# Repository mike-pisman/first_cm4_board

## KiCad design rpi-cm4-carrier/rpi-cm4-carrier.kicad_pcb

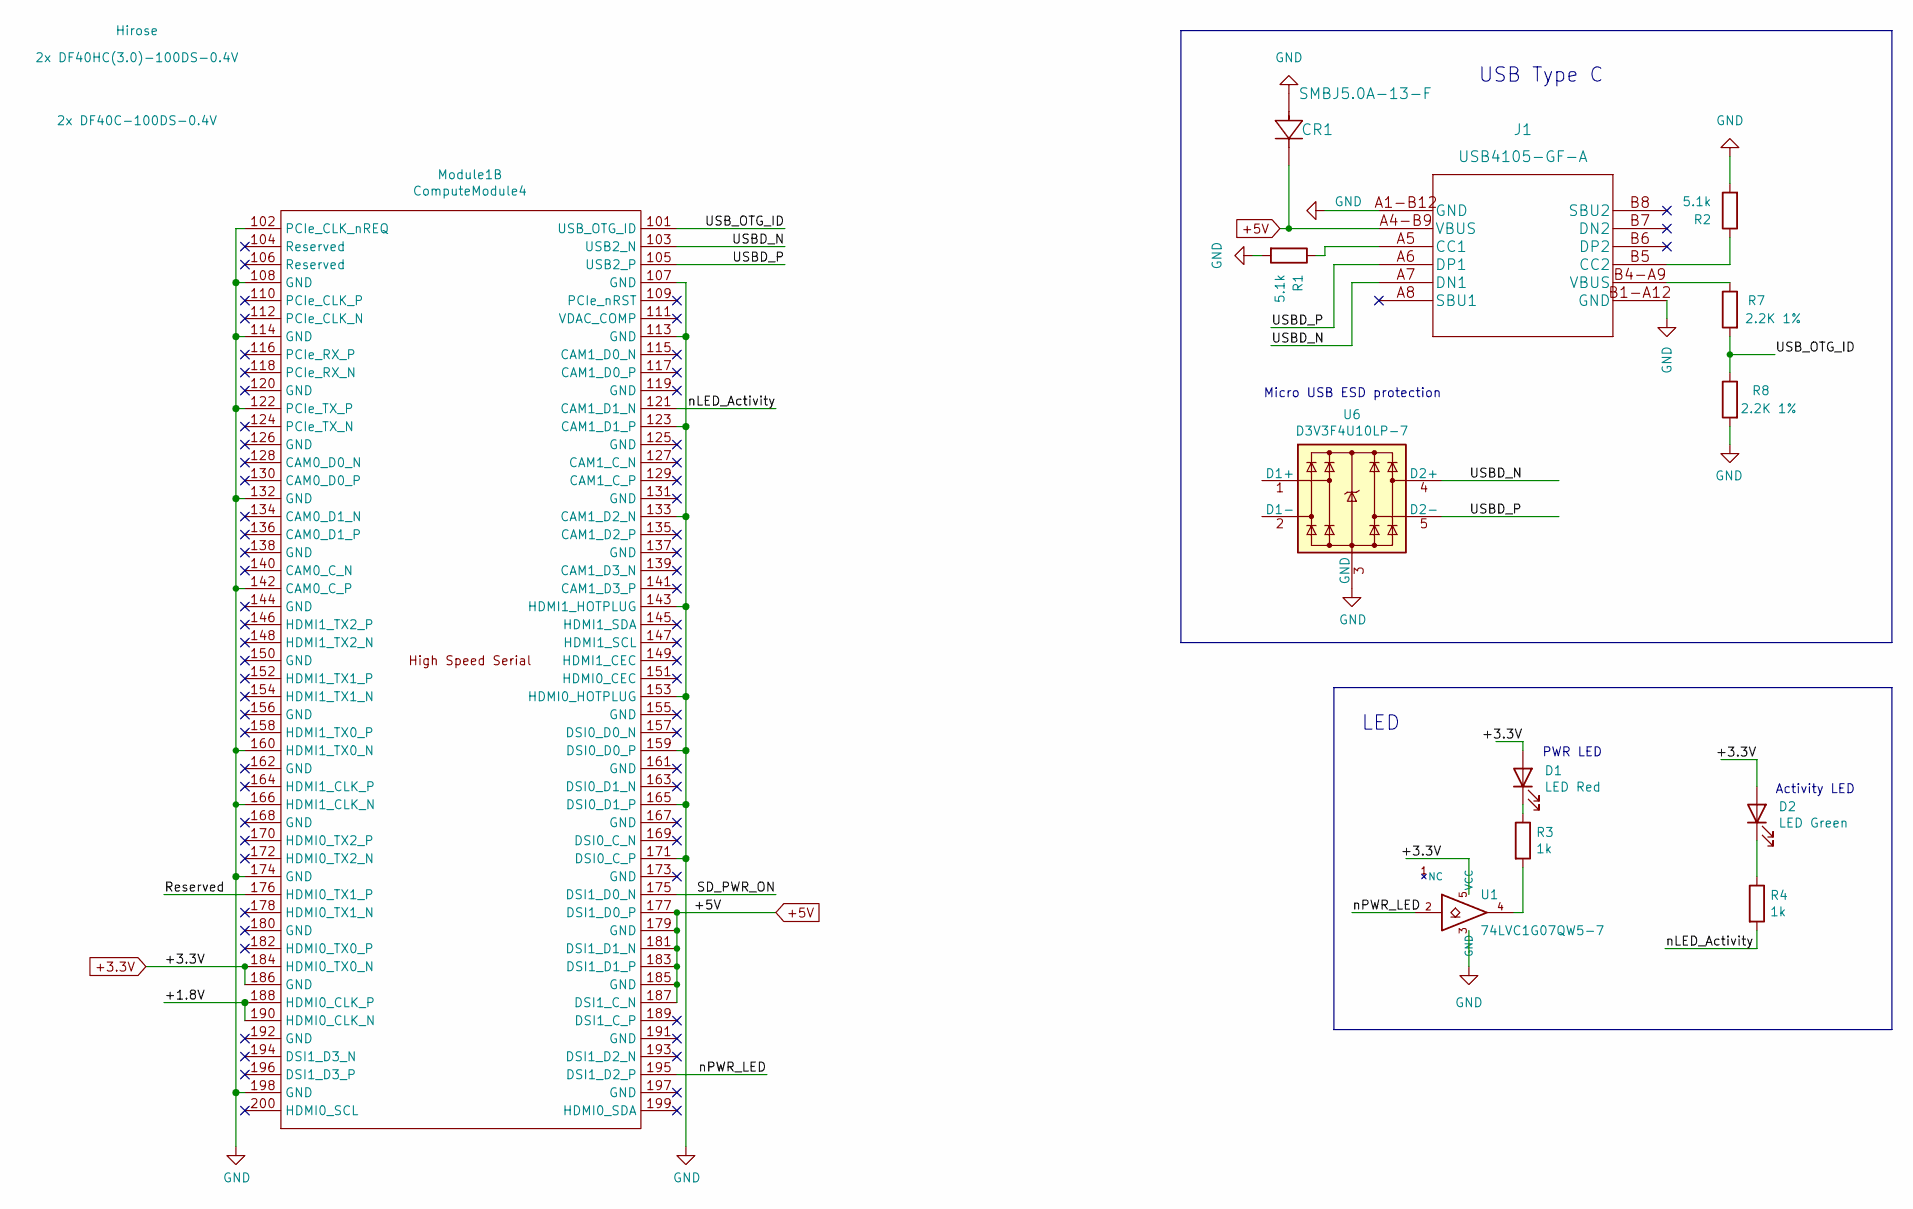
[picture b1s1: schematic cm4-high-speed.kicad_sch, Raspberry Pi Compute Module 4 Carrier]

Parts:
CR1: SMBJ5.0A-13-F; D_SMB; Digi-Key_PN SMBJ5.0A-FDICT-ND
D1: LED Red; LED_0603_1608Metric; Part Description Red 620nm LED Indication - Discrete 2.2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
D2: LED Green; LED_0603_1608Metric; Part Description Green 572nm LED Indication - Discrete 2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
J1: USB4105-GF-A; Digi-Key_PN 2073-USB4105-GF-ACT-ND
Module1: ComputeModule4; Raspberry-Pi-4-Compute-Module; Part Description 100 Position Connector Receptacle, Cent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; Digi-Key_PN 2x H11615CT-ND
R1, R2: 5.1k; R_0201_0603Metric_Pad0.64x0.40mm_HandSolder; Digi-Key_PN 311-5.10KHRCT-ND
R3, R4: 1k; R_0402_1005Metric; Part Description Resistor 1K M1005 1% 63mW
R7, R8: 2.2K 1%; R_0402_1005Metric; Part Description Resistor 2.2K M1005 1% 63mW
U1: 74LVC1G07QW5-7; SOT-353_SC-70-5; Part Description Buffer, Non-Inverting 1 Element 1 Bit p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; Digi-Key_PN 31-74LVC1G07QW5-7CT-ND
U6: D3V3F4U10LP-7; USON-10_2.5x1.0mm_P0.5mm; Part Description Quad TVS diode for high speed signals (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

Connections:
+3.3V: D1.2 (A), D2.2 (A), Module1.184 (HDMI0_TX0_N), Module1.186 (GND), U1.5 (VCC); also elsewhere on the board
+5V: CR1.1, J1.A4-B9 (VBUS), Module1.177 (DSI1_D0_P), Module1.179 (GND), Module1.181 (DSI1_D1_N), Module1.183 (DSI1_D1_P), Module1.185 (GND), Module1.187 (DSI1_C_N); also elsewhere on the board
/CM4 USB and LEDs/+1.8V: Module1.188 (HDMI0_CLK_P), Module1.190 (HDMI0_CLK_N)
/CM4 USB and LEDs/Reserved: Module1.176 (HDMI0_TX1_P)
/CM4 USB and LEDs/SD_PWR_ON: Module1.175 (DSI1_D0_N)
/CM4 USB and LEDs/USBD_N: J1.A7 (DN1), Module1.103 (USB2_N), U6.4 (D2+), U6.7
/CM4 USB and LEDs/USBD_P: J1.A6 (DP1), Module1.105 (USB2_P), U6.5 (D2-), U6.6
/CM4 USB and LEDs/USB_OTG_ID: Module1.101 (USB_OTG_ID), R7.2, R8.1
/CM4 USB and LEDs/nLED_Activity: Module1.121 (CAM1_D1_N), R4.2
/CM4 USB and LEDs/nPWR_LED: Module1.195 (DSI1_D2_P), U1.2
GND: CR1.2, J1.A1-B12 (GND), J1.B1-A12 (GND), Module1.102 (PCIe_CLK_nREQ), Module1.107 (GND), Module1.108 (GND), Module1.113 (GND), Module1.114 (GND), Module1.122 (PCIe_TX_P), Module1.123 (CAM1_D1_P), Module1.132 (GND), Module1.133 (CAM1_D2_N), Module1.142 (CAM0_C_P), Module1.143 (HDMI1_HOTPLUG), Module1.153 (HDMI0_HOTPLUG), Module1.159 (DSI0_D0_P), Module1.160 (HDMI1_TX0_N), Module1.165 (DSI0_D1_P), Module1.166 (HDMI1_CLK_N), Module1.171 (DSI0_C_P), Module1.174 (GND), Module1.198 (GND), R1.2, R2.2, R8.2, U1.3 (GND), U6.3 (GND), U6.8 (GND); also elsewhere on the board
unnamed: D1.1 (K), R3.1
unnamed: D2.1 (K), R4.1
unnamed: J1.A5 (CC1), R1.1
unnamed: J1.B4-A9 (VBUS), R7.1
unnamed: J1.B5 (CC2), R2.1
unnamed: R3.2, U1.4
unnamed: U6.1 (D1+), U6.10
unnamed: U6.2 (D1-), U6.9

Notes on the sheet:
Activity LED
USB Type C
LED
Micro USB ESD protection
PWR LED

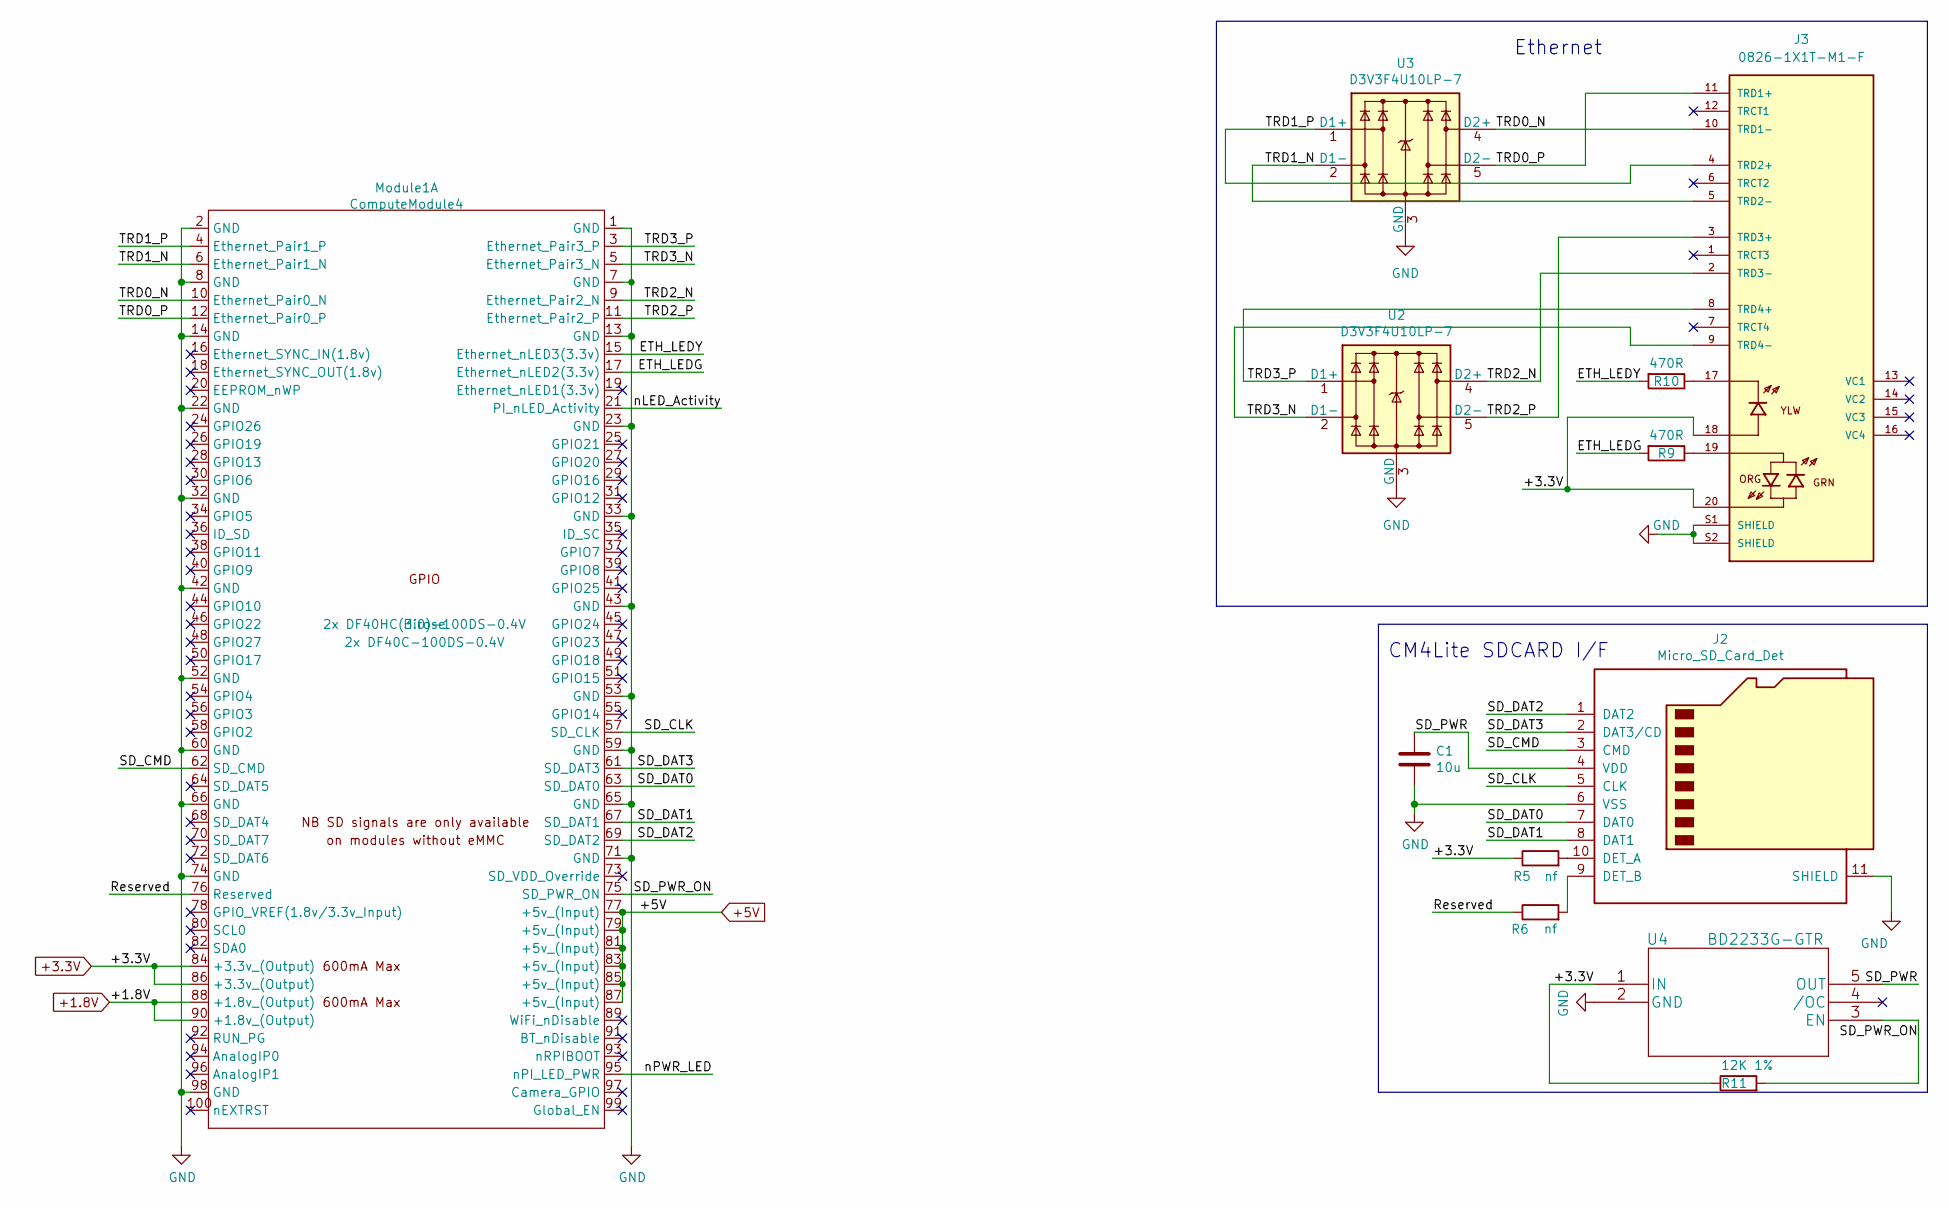
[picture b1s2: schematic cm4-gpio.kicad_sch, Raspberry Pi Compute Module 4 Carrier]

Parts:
C1: 10u; C_0805_2012Metric; Part Description 10uF 10% 10V Ceramic Capacitor X7R 0805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
J2: Micro_SD_Card_Det; SDCARD_MOLEX_503398-1892; Part Description 9 (8 + 1) Position Card Connector micro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; Digi-Key_PN 2073-MEM2051-00-195-00-ACT-ND
J3: 0826-1X1T-M1-F; Digi-Key_PN 380-1122-ND
Module1: ComputeModule4; Raspberry-Pi-4-Compute-Module; Part Description 100 Position Connector Receptacle, Cent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; Digi-Key_PN 2x H11615CT-ND
R5, R6: nf; R_0402_1005Metric; Part Description Resistor 1K M1005 1% 63mW
R9, R10: 470R; R_0402_1005Metric; Part Description Resistor 470R M1005 1% 63mW
R11: 12K 1%; R_0402_1005Metric; Part Description Resistor 12K M1005 1% 63mW
U2, U3: D3V3F4U10LP-7; USON-10_2.5x1.0mm_P0.5mm; Part Description Quad TVS diode for high speed signals (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; Digi-Key_PN D3V3F4U10LP-7DICT-ND
U4: BD2233G-GTR; SOT-23-5

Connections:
+1.8V: Module1.88 (+1.8v_(Output)), Module1.90 (+1.8v_(Output))
+3.3V: J3.18, J3.20, Module1.84 (+3.3v_(Output)), Module1.86 (+3.3v_(Output)), R5.1, R11.1, U4.1 (IN); also elsewhere on the board
+5V: Module1.77 (+5v_(Input)), Module1.79 (+5v_(Input)), Module1.81 (+5v_(Input)), Module1.83 (+5v_(Input)), Module1.85 (+5v_(Input)), Module1.87 (+5v_(Input)); also elsewhere on the board
/CM4 Ethernet and SD card/ETH_LEDG: Module1.17 (Ethernet_nLED2(3.3v)), R9.2
/CM4 Ethernet and SD card/ETH_LEDY: Module1.15 (Ethernet_nLED3(3.3v)), R10.2
/CM4 Ethernet and SD card/Reserved: Module1.76 (Reserved), R6.1
/CM4 Ethernet and SD card/SD_CLK: J2.5 (CLK), Module1.57 (SD_CLK)
/CM4 Ethernet and SD card/SD_CMD: J2.3 (CMD), Module1.62 (SD_CMD)
/CM4 Ethernet and SD card/SD_DAT0: J2.7 (DAT0), Module1.63 (SD_DAT0)
/CM4 Ethernet and SD card/SD_DAT1: J2.8 (DAT1), Module1.67 (SD_DAT1)
/CM4 Ethernet and SD card/SD_DAT2: J2.1 (DAT2), Module1.69 (SD_DAT2)
/CM4 Ethernet and SD card/SD_DAT3: J2.2 (DAT3/CD), Module1.61 (SD_DAT3)
/CM4 Ethernet and SD card/SD_PWR: C1.1, J2.4 (VDD), U4.5 (OUT)
/CM4 Ethernet and SD card/SD_PWR_ON: Module1.75 (SD_PWR_ON), R11.2, U4.3 (EN)
/CM4 Ethernet and SD card/TRD0_N: J3.10 (TRD1-), Module1.10 (Ethernet_Pair0_N), U3.4 (D2+), U3.7
/CM4 Ethernet and SD card/TRD0_P: J3.11 (TRD1+), Module1.12 (Ethernet_Pair0_P), U3.5 (D2-), U3.6
/CM4 Ethernet and SD card/TRD1_N: J3.5 (TRD2-), Module1.6 (Ethernet_Pair1_N), U3.2 (D1-), U3.9
/CM4 Ethernet and SD card/TRD1_P: J3.4 (TRD2+), Module1.4 (Ethernet_Pair1_P), U3.1 (D1+), U3.10
/CM4 Ethernet and SD card/TRD2_N: J3.2 (TRD3-), Module1.9 (Ethernet_Pair2_N), U2.4 (D2+), U2.7
/CM4 Ethernet and SD card/TRD2_P: J3.3 (TRD3+), Module1.11 (Ethernet_Pair2_P), U2.5 (D2-), U2.6
/CM4 Ethernet and SD card/TRD3_N: J3.9 (TRD4-), Module1.5 (Ethernet_Pair3_N), U2.2 (D1-), U2.9
/CM4 Ethernet and SD card/TRD3_P: J3.8 (TRD4+), Module1.3 (Ethernet_Pair3_P), U2.1 (D1+), U2.10
/CM4 Ethernet and SD card/nLED_Activity: Module1.21 (PI_nLED_Activity)
/CM4 Ethernet and SD card/nPWR_LED: Module1.95 (nPI_LED_PWR)
GND: C1.2, J2.6 (VSS), J2.11 (SHIELD), J3.S1 (SHIELD), J3.S2 (SHIELD), Module1.1 (GND), Module1.2 (GND), Module1.7 (GND), Module1.8 (GND), Module1.13 (GND), Module1.14 (GND), Module1.22 (GND), Module1.23 (GND), Module1.32 (GND), Module1.33 (GND), Module1.42 (GND), Module1.43 (GND), Module1.52 (GND), Module1.53 (GND), Module1.59 (GND), Module1.60 (GND), Module1.65 (GND), Module1.66 (GND), Module1.71 (GND), Module1.74 (GND), Module1.98 (GND), U2.3 (GND), U2.8 (GND), U3.3 (GND), U3.8 (GND), U4.2 (GND); also elsewhere on the board
unnamed: J2.9 (DET_B), R6.2
unnamed: J2.10 (DET_A), R5.2
unnamed: J3.17, R10.1
unnamed: J3.19, R9.1

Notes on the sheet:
CM4Lite SDCARD I/F
Ethernet

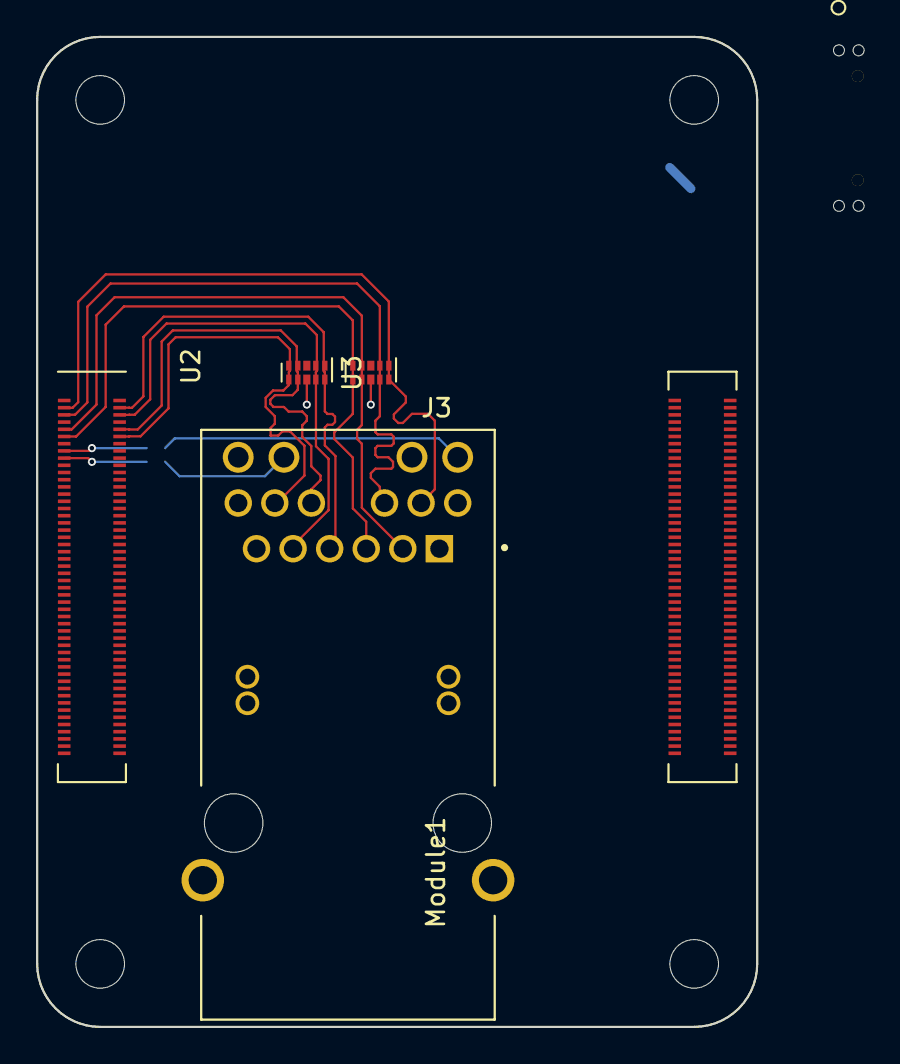
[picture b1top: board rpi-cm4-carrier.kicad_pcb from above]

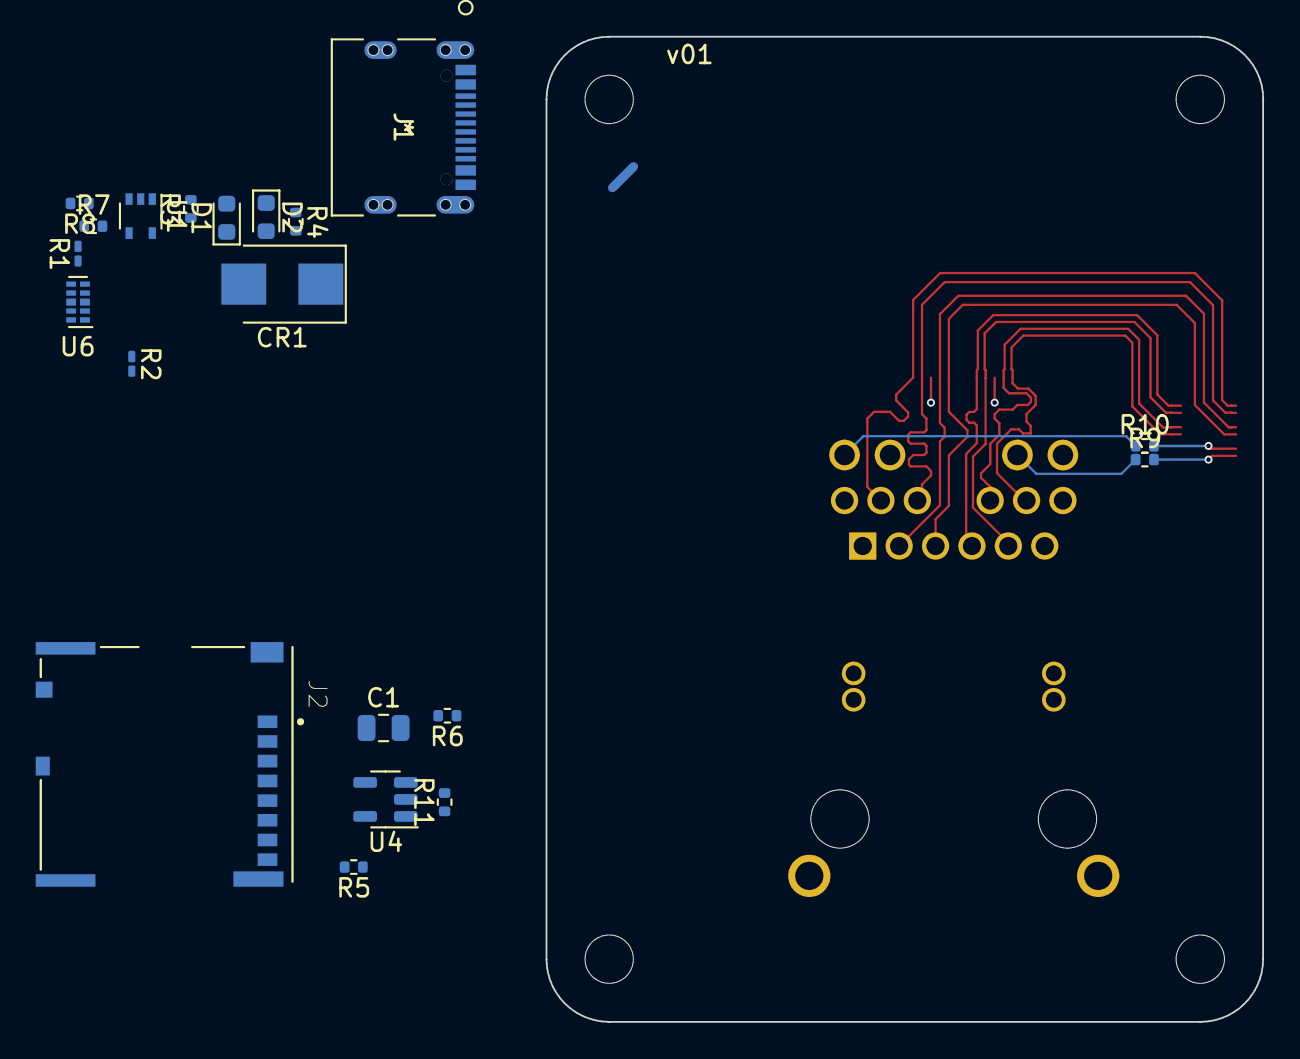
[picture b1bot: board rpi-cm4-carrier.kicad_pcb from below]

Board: 2 copper layers, 40.0 x 55.0 mm, 24 parts (20 on the bottom side), 41 nets.

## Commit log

2022-07-22 Wired Ethernet data

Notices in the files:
rpi-cm4-carrier/cm4-gpio.kicad_sch:
creativecommons.org/licenses/by-sa/4.0
License: CC BY 4.0
rpi-cm4-carrier/rpi-cm4-carrier.kicad_pcb:
creativecommons.org/licenses/by/4.0
parts and their libraries:
Copyright 2021 Accelerated Designs. All rights reserved.
